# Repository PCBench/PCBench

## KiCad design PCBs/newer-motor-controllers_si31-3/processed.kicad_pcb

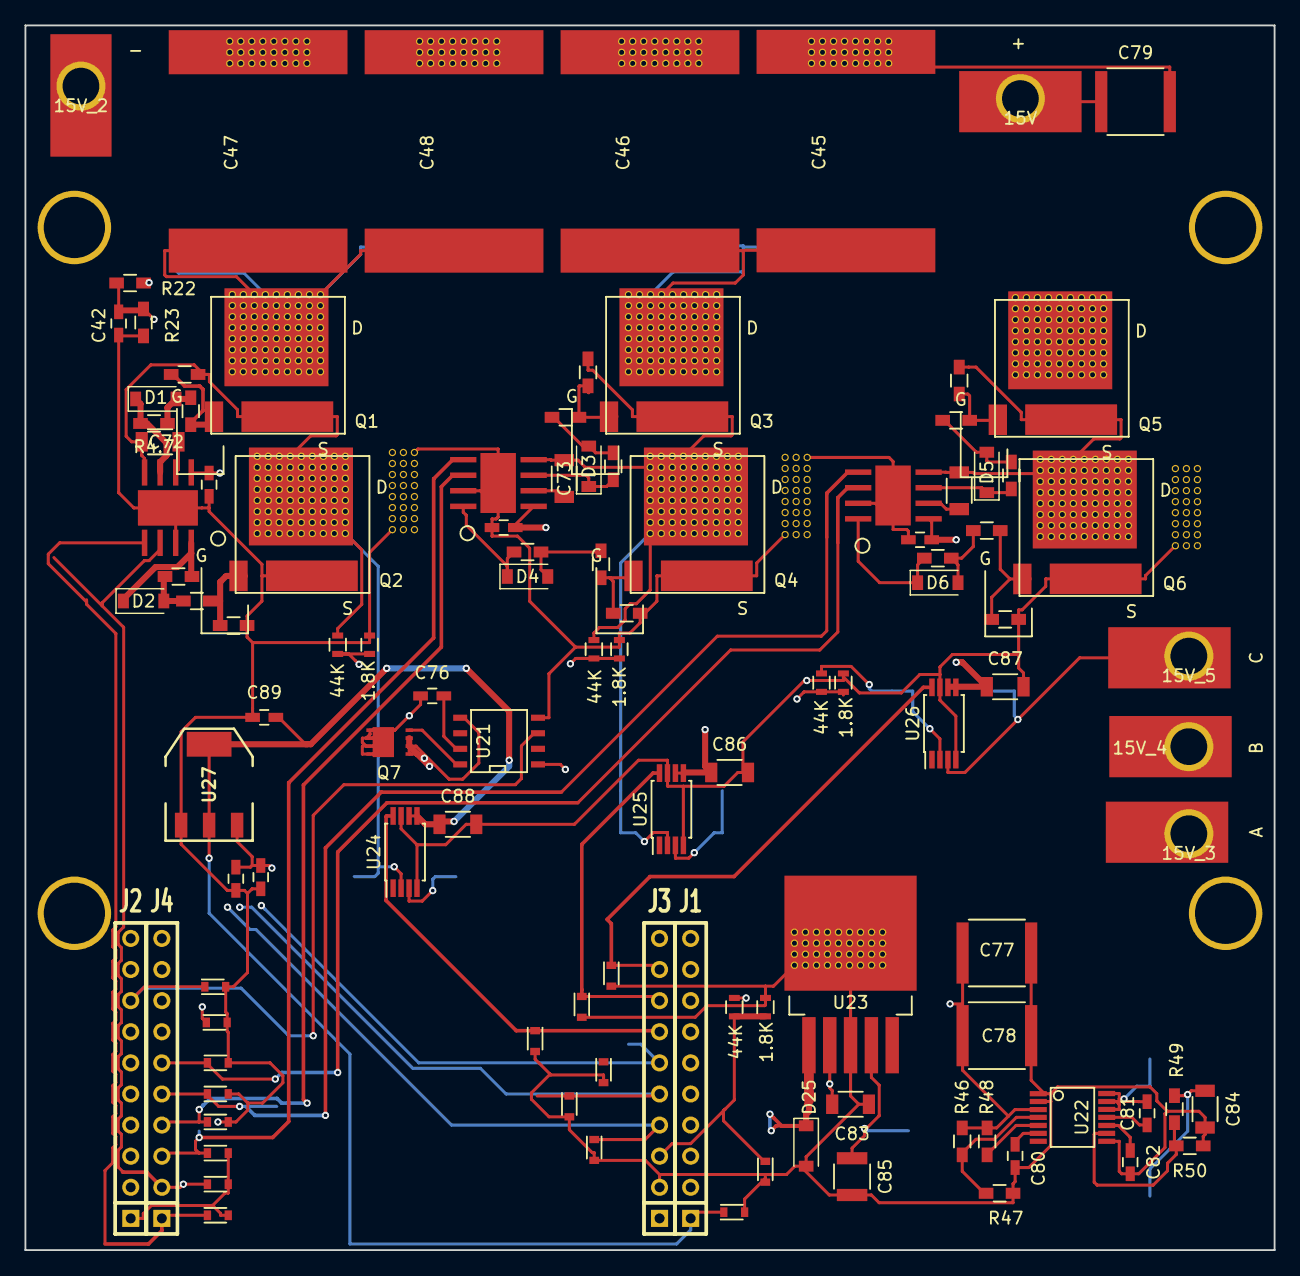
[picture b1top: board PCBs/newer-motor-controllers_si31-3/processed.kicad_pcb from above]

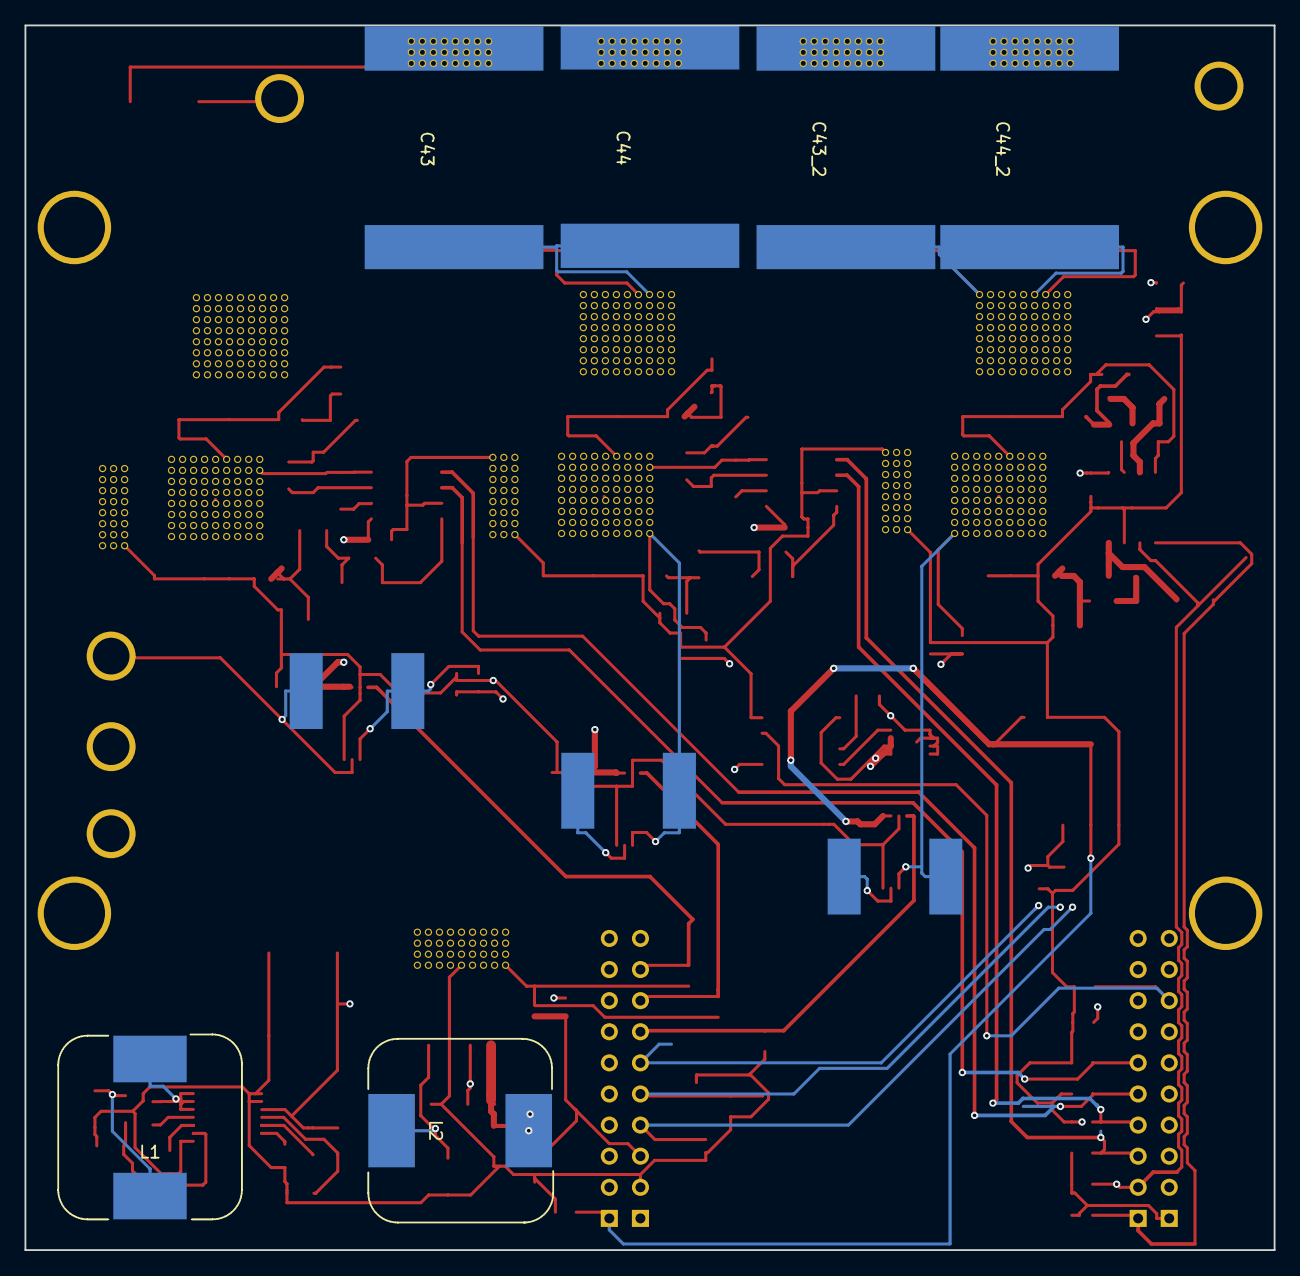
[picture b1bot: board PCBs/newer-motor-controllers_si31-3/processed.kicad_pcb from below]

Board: 4 copper layers, 102.0 x 100.0 mm, 123 parts (9 on the bottom side), 58 nets.

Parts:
10k1, 10k2, 10k3, 10k4, 10k5, 10k6: R_Small; R_0603_HandSoldering
15V, 15V_2, 15V_3, 15V_4, 15V_5: via
+: V+; SolderWirePad_single_SMD_5x10mm
-: V-; SolderWirePad_single_SMD_5x10mm
A: motor_A; SolderWirePad_single_SMD_5x10mm
B: motor_B; SolderWirePad_single_SMD_5x10mm
C: motor_C; SolderWirePad_single_SMD_5x10mm
C42: 2.2uf; C_0603_HandSoldering
C43, C43_2, C44, C44_2, C45, C46, C47, C48: 4.7uf; cap_6065
C69, C70, C71, C82, C89: 1uf; C_0603_HandSoldering
C72, C73, C74, C86, C87, C88: 0.1uf; C_1206
C75: 0.1uf; C_0603_HandSoldering
C76: 10pf; C_0603_HandSoldering
C77, C78, C79: 1uf 250V; C_2220
C80: 22nf; C_0603_HandSoldering
C81: 10nf; C_0603_HandSoldering
C83, C84: 10uf; C_1206
C85: 100uf; C_1210
C90: 10uf; C_0603_HandSoldering
D1, D2, D3, D4, D5, D6: D_Schottky_Small; SOD-123
D8, D9, D10, D11, D12, D13, D14, D15, D16, D17, D18, D19, D20, D21, D22, D23: TVS; D_0603
D25: D_Schottky; SOD-123
J1: Ti_Booster_40_J1; SIL-10J1
J2: Ti_Booster_40_J2; SIL-10J2
J3: Ti_Booster_40_J3; SIL-10J3
J4: Ti_Booster_40_J4; SIL-10J4
L1, L2: INDUCTOR; MSS1583-154KED
Q1, Q2, Q3, Q4, Q5, Q6: FDMT-800; P-PG-HSOF-08
Q7: Q_NMOS_DSG; VSONP-8
R4.1, R4.2, R4.3, R4.4, R4.5, R4.7: R_Small; R_0603_HandSoldering
R22: NTC 10k; R_0603_HandSoldering
R23: 10k; R_0603_HandSoldering
R40, R41, R42, R42_2: 1.8K; R_0603
R43, R44, R45, R45_2: 44K; R_0603
R46: 75k; R_0603_HandSoldering
R47: 4.42k; R_0603_HandSoldering
R48: 499k; R_0603_HandSoldering
R49: 13k; R_0603_HandSoldering
R50: 2k; R_0603_HandSoldering
R51, R52, R53: 0.001R; SHUNT_CSS2H-3920
U18, U19, U20: UCC27210; SO_PowerPAD-8
U21: Si8751; SOIC-8-N
U22: LM5161; SSOP-14
U23: LM2595; TO-263-5Lead
U24, U25, U26: INA240; TSSOP-8_4.4x3mm_Pitch0.65mm
U27: NCP1117ST33T3G; SOT-223
ferrite1, ferrite2, ferrite3, ferrite4, ferrite5, ferrite6: R_Small; R_0603_HandSoldering

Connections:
+5V: C75.1, C85.1, C90.1, J3.1, L2.2, U21.1, U23.4, U27.3
+15V: C76.1, C83.1, C84.1, L1.2, Q7.1, R49.1, U23.2
/Ti_120vgate/vsense_a: D12.1, J3.4, R40.2, R43.2
/Ti_120vgate/vsense_b: D13.1, J3.5, R41.2, R44.2
/Ti_120vgate/vsense_c: J3.6, R42.2, R45.2
/VBUS: 15V.1, +.1, C43.2, C43_2.2, C44.2, C44_2.2, C45.2, C46.2, C47.2, C48.2, C77.1, C78.1, C79.1, Q1.1, Q3.1, Q5.1, R45_2.1, R46.1, R48.2, U22.3
/connector/CurrentA: D15.1, J3.7, U24.8
/connector/CurrentB: D16.1, J3.8, U25.8
/connector/CurrentC: D17.1, J3.9, U26.8
/connector/EN_GATE: D10.1, J2.8, U21.3
/connector/PWM_H1: D18.1, J4.1, U18.5
/connector/PWM_H2: D20.1, J4.3, U19.5
/connector/PWM_H3: D22.1, J4.5, U20.5
/connector/PWM_L1: D19.1, J4.2, U18.6
/connector/PWM_L2: D21.1, J4.4, U19.6
/connector/PWM_L3: D23.1, J4.6, U20.6
/connector/TEMP: C42.1, D8.1, J2.3, R22.2, R23.1
/connector/VBUS_sense: D11.1, J3.3, R42_2.2, R45_2.2
/current_sense_80v/PHASE_1: 15V_3.1, A.1, R53.1, U24.3
/current_sense_80v/PHASE_2: 15V_4.1, B.1, R52.1, U25.3
/current_sense_80v/PHASE_3: 15V_5.1, C.1, R51.1, U26.3
/mosfet/H1: D1.1, R4.7.2, U18.3
/mosfet/H2: D3.1, R4.2.2, U19.3
/mosfet/H3: D5.1, R4.4.2, U20.3
/mosfet/L1: D2.1, R4.1.2, U18.8
/mosfet/L2: D4.1, R4.3.2, U19.8
/mosfet/L3: D6.1, R4.5.2, U20.8
/mosfet/phase_a_in: 10k1.2, C72.1, Q1.2, Q2.1, R43.1, R53.2, U18.4, U24.2
/mosfet/phase_b_in: 10k3.2, C73.1, Q3.2, Q4.1, R44.1, R52.2, U19.4, U25.2
/mosfet/phase_c_in: 10k5.2, C74.1, Q5.2, Q6.1, R45.1, R51.2, U20.4, U26.2
GND: 10k2.2, 10k4.2, 10k6.2, 15V_2.1, -.1, C42.2, C43.1, C43_2.1, C44.1, C44_2.1, C45.1, C46.1, C47.1, C48.1, C69.2, C70.2, C71.2, C75.2, C77.2, C78.2, C79.2, C80.2, C82.2, C83.2, C84.2, C85.2, C86.2, C87.2, C88.2, C89.2, C90.2, D8.2, D9.2, D10.2, D11.2, D12.2, D13.2, D14.2, D15.2, D16.2, D17.2, D18.2, D19.2, D20.2, D21.2, D22.2, D23.2, D25.2, J2.1, J3.2, Q2.2, Q4.2, Q6.2, R23.2, R40.1, R41.1, R42.1, R42_2.1, R47.2, R50.2, U18.7, U18.pad, U19.7, U19.pad, U20.7, U20.pad, U21.4, U22.1, U22.2, U22.8, U23.3, U24.4, U24.7, U25.4, U25.7, U26.4, U26.7, U27.1
unnamed: 10k1.1, Q1.3, ferrite1.1
unnamed: 10k2.1, Q2.3, ferrite2.1
unnamed: 10k3.1, Q3.3, ferrite3.1
unnamed: 10k4.1, Q4.3, ferrite4.1
unnamed: 10k5.1, Q5.3, ferrite5.1
unnamed: 10k6.1, Q6.3, ferrite6.1
unnamed: C69.1, C70.1, C71.1, Q7.2, U18.1, U19.1, U20.1, U21.5
unnamed: C72.2, U18.2
unnamed: C73.2, U19.2
unnamed: C74.2, U20.2
unnamed: C76.2, U21.7
unnamed: C80.1, U22.6
unnamed: C81.1, L1.1, U22.12, U22.13, U22.14
unnamed: C81.2, U22.11
unnamed: C82.1, U22.10
unnamed: C86.1, C87.1, C88.1, C89.1, D9.1, J1.1, R22.1, U24.5, U24.6, U25.5, U25.6, U26.5, U26.6, U27.2
unnamed: D1.2, R4.7.1, ferrite1.2
unnamed: D2.2, R4.1.1, ferrite2.2
unnamed: D3.2, R4.2.1, ferrite3.2
unnamed: D4.2, R4.3.1, ferrite4.2
unnamed: D5.2, R4.4.1, ferrite5.2
unnamed: D6.2, R4.5.1, ferrite6.2
unnamed: D25.1, L2.1, U23.1
unnamed: Q7.3, U21.8
unnamed: R46.2, R47.1, U22.4
unnamed: R48.1, U22.5
unnamed: R49.2, R50.1, U22.9

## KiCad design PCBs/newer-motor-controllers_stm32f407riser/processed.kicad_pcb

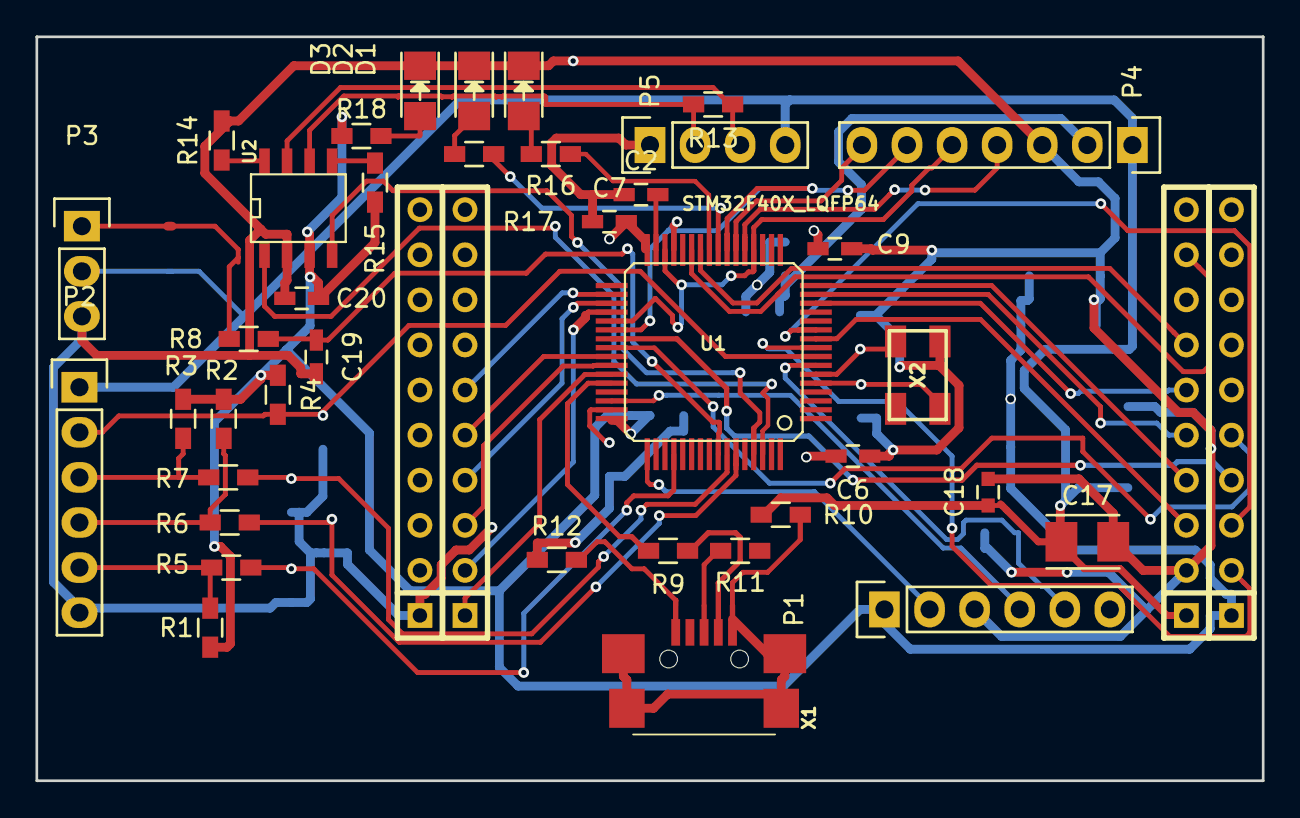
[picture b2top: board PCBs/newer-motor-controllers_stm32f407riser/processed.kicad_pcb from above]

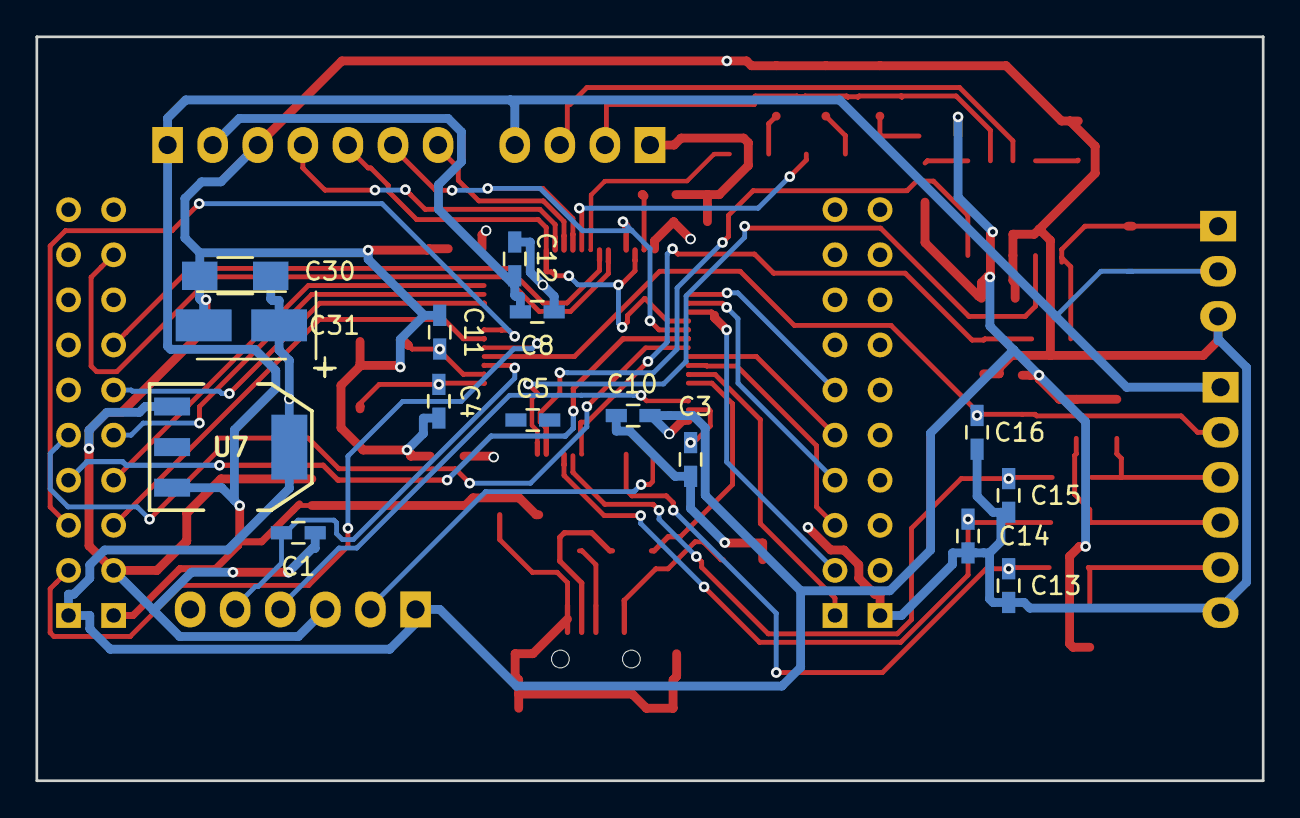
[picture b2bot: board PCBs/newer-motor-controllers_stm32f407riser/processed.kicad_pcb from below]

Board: 4 copper layers, 69.1 x 41.9 mm, 57 parts (15 on the bottom side), 55 nets.

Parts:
C1: 100pf; C_0603_HandSoldering
C2, C3, C5, C6, C7, C8, C9, C10, C12, C20: 2.2uf; C_0603_HandSoldering
C4, C11: 15pf; C_0603_HandSoldering
C13, C14, C15, C16: 4.7nf; C_0603_HandSoldering
C17: 100uf; TantalC_SizeB_EIA-3528_Reflow
C18: 10uf; C_0603
C19: 100nf; C_0603_HandSoldering
C30: 2.2uf; C_1206_HandSoldering
C31: 100uf; TantalC_SizeB_EIA-3528_HandSoldering
D1, D2, D3: LED; LED_1206
J1: Ti_Booster_40_J1; SIL-10J1
J2: Ti_Booster_40_J2; SIL-10J2
J3: Ti_Booster_40_J3; SIL-10J3
J4: Ti_Booster_40_J4; SIL-10J4
P1, P2: CONN_01X06; Pin_Header_Straight_1x06
P3: CONN_01X03; Pin_Header_Straight_1x03
P4: CONN_01X07; Pin_Header_Straight_1x07
P5: CONN_01X04; Pin_Header_Straight_1x04
R1, R2, R3, R8, R18: 2k; R_0603_HandSoldering
R4, R5, R6, R7, R14, R15: 10k; R_0603_HandSoldering
R9, R11: 20r; R_0603_HandSoldering
R10, R12: 0r; R_0603_HandSoldering
R13: 120R; R_0603_HandSoldering
R16, R17: 100r; R_0603_HandSoldering
U1: STM32F40X_LQFP64; lqfp64_pad_mod_hand
U2: MCP2551-I/SN; SOIC-8-W
U7: NCP1117ST33T3G; SOT-223
X1: MINI-USB-SCHIELD-32005-201; USB-UX60R-MB-5ST
X2: 8MHz 10ppm; Crystal_5x3mm

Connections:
+3V3: C6.2, C7.2, C8.2, C9.2, C10.1, C12.1, C20.1, C30.1, C31.1, J1.1, P1.1, P4.2, R1.1, R2.1, R3.1, R4.1, R15.1, R18.2, U1.32, U1.48, U2.3, U7.2
+5V: C17.1, C18.1, J3.1, P2.1, P3.2, P4.1, P5.4, R10.1, U7.3
/Power MOSFETS/CAN_RX: U1.61, U2.4
/Power MOSFETS/CAN_TX: U1.62, U2.1
/Power MOSFETS/CurrentA: J3.7, U1.26
/Power MOSFETS/CurrentC: J3.9, U1.27
/Power MOSFETS/H1: J4.1, U1.43
/Power MOSFETS/H2: J4.3, U1.42
/Power MOSFETS/H3: J4.5, U1.41
/Power MOSFETS/HALL_1: C15.1, R7.1, U1.58
/Power MOSFETS/HALL_2: C14.1, R6.1, U1.59
/Power MOSFETS/HALL_3: C13.1, R5.1, U1.52
/Power MOSFETS/L1: J4.2, U1.36
/Power MOSFETS/L2: J4.4, U1.35
/Power MOSFETS/L3: J4.6, U1.34
/Power MOSFETS/LED_GREEN: R16.2, U1.25
/Power MOSFETS/LED_RED: R17.2, U1.24
/Power MOSFETS/MISO_ADC_EXT: P4.7, U1.22
/Power MOSFETS/PC1: J1.2, U1.9
/Power MOSFETS/PC3: J1.3, U1.11
/Power MOSFETS/PC8: J1.4, U1.39
/Power MOSFETS/PC9: J1.5, U1.40
/Power MOSFETS/RX_SCL_MOSI: P4.6, U1.23, U1.29, U1.38
/Power MOSFETS/SCK_ADC_EX: P4.4, U1.21
/Power MOSFETS/SERVO: C19.2, R8.2, U1.57
/Power MOSFETS/TEMP_MOTOR: C16.1, P2.2, R4.2, U1.8
/Power MOSFETS/TX_SDA_NSS: P4.5, U1.20, U1.30, U1.37
/Power MOSFETS/USB_DM: R9.2, U1.44
/Power MOSFETS/VBUS_SENSE: J3.3, U1.10
/Power MOSFETS/V_SENSE1: J3.4, U1.16
/Power MOSFETS/V_SENSE2: J3.5, U1.15
/Power MOSFETS/V_SENSE3: J3.6, U1.14
GND: C1.1, C2.1, C3.1, C4.1, C6.1, C7.1, C8.1, C9.1, C10.2, C11.1, C12.2, C13.2, C14.2, C15.2, C16.2, C17.2, C18.2, C19.1, C20.2, C30.2, C31.2, D1.1, D2.1, D3.1, J2.1, J3.2, P1.3, P2.6, P3.3, P4.3, P5.1, R12.1, R14.2, U2.2, U7.1, X2.3
unnamed: C1.2, P1.5, U1.7
unnamed: C2.2, U1.31
unnamed: C3.2, U1.47
unnamed: C4.2, U1.5, X2.1
unnamed: C11.2, U1.6, X2.2
unnamed: D1.2, R16.1
unnamed: D2.2, R17.1
unnamed: D3.2, R18.1
unnamed: P1.2, U1.49
unnamed: P1.4, U1.46
unnamed: P2.3, R3.2, R7.2
unnamed: P2.4, R2.2, R6.2
unnamed: P2.5, R1.2, R5.2
unnamed: P3.1, R8.1
unnamed: P5.2, R13.2, U2.6
unnamed: P5.3, R13.1, U2.7
unnamed: R9.1, X1.2
unnamed: R10.2, X1.1, X1.5
unnamed: R11.1, X1.3
unnamed: R12.2, X1.5
unnamed: R14.1, U2.8
unnamed: R15.2, U2.5

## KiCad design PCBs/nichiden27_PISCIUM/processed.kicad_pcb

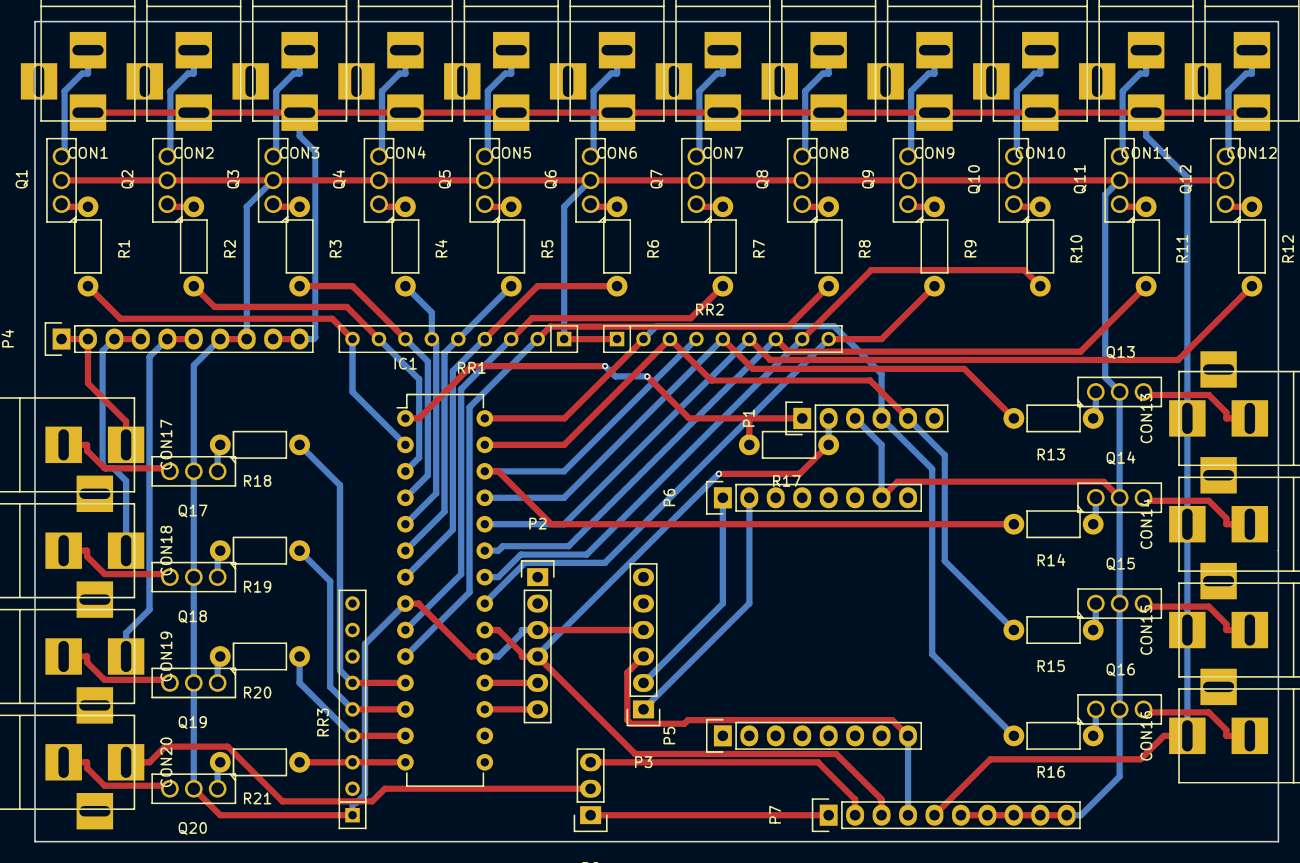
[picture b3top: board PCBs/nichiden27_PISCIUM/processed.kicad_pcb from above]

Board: 2 copper layers, 119.4 x 78.7 mm, 73 parts (0 on the bottom side), 75 nets.

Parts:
CON1, CON2, CON3, CON4, CON5, CON6, CON7, CON8, CON9, CON10, CON11, CON12, CON13, CON14, CON15, CON16, CON17, CON18, CON19, CON20: BARREL_JACK
IC1: PIC16F1938; DIP-28_W7.62mm
P1, P2, P3: CONN_01X06; Pin_Header_Straight_1x06
P4, P7: CONN_01X10; Pin_Header_Straight_1x10
P5, P6: CONN_01X08; Pin_Header_Straight_1x08
P8: GINGA_voltage_selector; Pin_Header_Straight_1x03
Q1, Q2, Q3, Q4, Q5, Q6, Q7, Q8, Q9, Q10, Q11, Q12, Q13, Q14, Q15, Q16, Q17, Q18, Q19, Q20: EKI04047; SOT126_SOT32_Housing_Vertical
R1, R2, R3, R4, R5, R6, R7, R8, R9, R10, R11, R12, R13, R14, R15, R16, R18, R19, R20, R21: 100; Resistor_Horizontal_RM7mm
R17: 4.7k-10k; Resistor_Horizontal_RM7mm
RR1, RR2, RR3: RR8_100k; Resistor_Array_SIP8

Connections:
3.3V_LOGIC: P3.3, P5.8, P7.4
5V_GINGA: P7.1, P8.1
5V_ITTOU1: CON19.1, P4.5, P4.6
5V_LOGIC: IC1.20, P1.2, P2.4, P7.3, R17.1
12V_GINGA: P7.2, P8.3
12V_KOUTOU11: CON17.1, P4.1, P4.2
12V_KOUTOU21: CON18.1, P4.3, P4.4
12V_SEIZAE1: CON1.1, CON2.1, CON3.1, CON4.1, CON5.1, CON6.1, CON7.1, CON8.1, CON9.1, CON10.1, CON11.1, CON12.1, CON13.1, CON14.1, CON15.1, CON16.1, P4.9, P4.10, P7.5
+12V: IC1.8, IC1.19, P1.3, P2.3, P3.4, P4.7, P4.8, P6.7, P7.6, P7.7, P7.8, P7.9, P7.10, Q1.2, Q2.2, Q3.2, Q4.2, Q5.2, Q6.2, Q7.2, Q8.2, Q9.2, Q10.2, Q11.2, Q12.2, Q13.2, Q14.2, Q15.2, Q16.2, Q17.2, Q18.2, Q19.2, Q20.2, RR1.1, RR2.1, RR3.1
unnamed: CON1.2, Q1.3
unnamed: CON2.2, Q2.3
unnamed: CON3.2, Q3.3
unnamed: CON4.2, Q4.3
unnamed: CON5.2, Q5.3
unnamed: CON6.2, Q6.3
unnamed: CON7.2, Q7.3
unnamed: CON8.2, Q8.3
unnamed: CON9.2, Q9.3
unnamed: CON10.2, Q10.3
unnamed: CON11.2, Q11.3
unnamed: CON12.2, Q12.3
unnamed: CON13.2, Q13.3
unnamed: CON14.2, Q14.3
unnamed: CON15.2, Q15.3
unnamed: CON16.2, Q16.3
unnamed: CON17.2, Q17.3
unnamed: CON18.2, Q18.3
unnamed: CON19.2, Q19.3
unnamed: CON20.2, Q20.3
unnamed: IC1.1, P1.1, R17.2
unnamed: IC1.2, R1.2, RR1.9
unnamed: IC1.3, R2.2, RR1.8
unnamed: IC1.4, R3.2, RR1.7
unnamed: IC1.5, R4.2, RR1.6
unnamed: IC1.6, R5.2, RR1.5
unnamed: IC1.7, R6.2, RR1.4
unnamed: IC1.9, R7.2, RR1.3
unnamed: IC1.10, R8.2, RR1.2
unnamed: IC1.11, R18.1, RR3.6
unnamed: IC1.12, R19.1, RR3.5
unnamed: IC1.13, R20.1, RR3.4
unnamed: IC1.14, R21.1, RR3.3
unnamed: IC1.17, P2.6
unnamed: IC1.18, P2.5
unnamed: IC1.21, R9.2, RR2.9
unnamed: IC1.22, R10.2, RR2.8
unnamed: IC1.23, R11.2, RR2.7
unnamed: IC1.24, R12.2, RR2.6
unnamed: IC1.25, R13.2, RR2.5
unnamed: IC1.26, R14.2, RR2.4
unnamed: IC1.27, P1.5, R15.2, RR2.3
unnamed: IC1.28, P1.4, R16.2, RR2.2
unnamed: P3.1, P6.2
unnamed: P3.2, P6.1
unnamed: Q1.1, R1.1
unnamed: Q2.1, R2.1
unnamed: Q3.1, R3.1
unnamed: Q4.1, R4.1
unnamed: Q5.1, R5.1
unnamed: Q6.1, R6.1
unnamed: Q7.1, R7.1
unnamed: Q8.1, R8.1
unnamed: Q9.1, R9.1
unnamed: Q10.1, R10.1
unnamed: Q11.1, R11.1
unnamed: Q12.1, R12.1
unnamed: Q13.1, R13.1
unnamed: Q14.1, R14.1
unnamed: Q15.1, R15.1
unnamed: Q16.1, R16.1
unnamed: Q17.1, R18.2
unnamed: Q18.1, R19.2
unnamed: Q19.1, R20.2
unnamed: Q20.1, R21.2
VCC_GINGA: CON20.1, P8.2

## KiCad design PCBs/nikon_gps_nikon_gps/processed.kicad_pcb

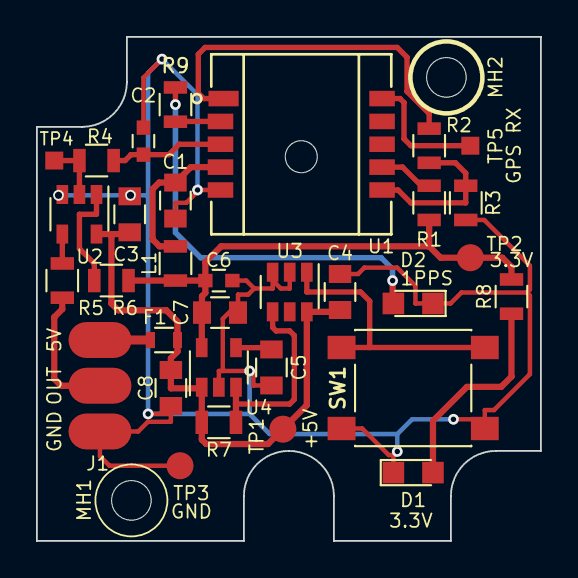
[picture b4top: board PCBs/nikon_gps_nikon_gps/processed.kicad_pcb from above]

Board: 2 copper layers, 28.0 x 28.0 mm, 34 parts (0 on the bottom side), 20 nets.

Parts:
C1, C3, C4: 100nF; C_0805
C2: 18pF; C_0603
C5: 470pF; C_0805
C6: 1nF; C_0603
C7, C8: 10uF; C_0805
D1: Red; LED_0805
D2: Blue; LED_0805
F1: 0.1A; R_0603
J1: Conn_01x03; Connection_Pads_03
L1: 600Ohm; L_0805
MH1, MH2: M2 screw; MountingHole_2.2mm_M2_DIN965
R1, R3: 10K; R_0805
R2, R4, R5: 33; R_0805
R6, R7: 0; R_0805
R8: 330; R_0805
R9: 270; R_0805
SW1: ON/OFF; SW_SPST_PTS645
TP1: 5V; Measurement_Point_Round-SMD-Pad_Small
TP2: 3.3V; Measurement_Point_Round-SMD-Pad_Small
TP3: GND; Measurement_Point_Round-SMD-Pad_Small
TP4: GPS TX; Measurement_Point_Square-SMD_1.0mmx1.0mm
TP5: GPS RX; Measurement_Point_Square-SMD_1.0mmx1.0mm
U1: Hornet ORG1411; ORG1411_GPS
U2: SN74LV1T126_ALT; SOT-23-5
U3: MAX16054; SOT-23-6
U4: MIC5205-3.3; SOT-23-5

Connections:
+3V3: C6.1, C7.1, L1.2, R1.1, R6.1, R8.2, TP2.1, U4.5
+5V: C3.2, C4.2, C8.1, F1.1, R7.2, TP1.1, U2.5, U3.6, U4.1
/1PPS: R9.2, U1.2
/3.3V_EN: R7.1, U3.4, U4.3
/3.3V_GPS: C1.2, L1.1, U1.4
/BUF_EN: R6.2, U2.1
/BUF_IN: R4.2, TP4.1, U2.2
/BUF_OUT: R5.1, U2.4
/C_BYP: C5.1, U4.4
/GPS_OUT: J1.2, R5.2
/GPS_RX: TP5.1, U1.10
/GPS_TX: C2.1, R4.1, U1.3
/ON_OFF: R2.2, U1.1
/ON_SW: SW1.2, U3.1
/WAKEUP: R2.1, R3.1, U1.6
/~CTS: R1.2, U1.7
GND: C1.1, C2.2, C3.1, C4.1, C5.2, C6.2, C7.2, C8.2, D1.1, D2.1, J1.3, R3.2, SW1.1, TP3.1, U1.5, U2.3, U3.2, U3.3, U4.2
unnamed: D1.2, R8.1
unnamed: D2.2, R9.1
unnamed: F1.2, J1.1

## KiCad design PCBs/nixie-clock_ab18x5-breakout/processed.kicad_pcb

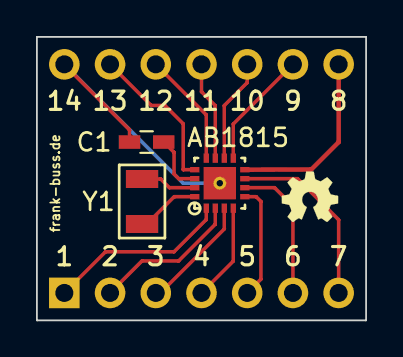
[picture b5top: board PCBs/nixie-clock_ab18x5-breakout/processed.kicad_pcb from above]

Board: 2 copper layers, 18.3 x 15.7 mm, 5 parts (0 on the bottom side), 17 nets.

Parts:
C1: 47pF; C_0603_HandSoldering
J1: CONN_01X07; Pin_Header_Straight_1x07_Pitch2.54mm2
J2: CONN_01X07; Pin_Header_Straight_1x07_Pitch2.54mm
U1: AB1815; qfn16
Y1: Crystal; crystal

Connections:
/CLKOUT/nIRQ3: J2.7, U1.8
/EXTI: J2.5, U1.10
/FOUT/nIRQ: J2.4, U1.11
/PSW/nIRQ2: J1.4, U1.4
/SCL: J1.7, U1.7
/SDI: J2.6, U1.9
/SDO: J1.6, U1.6
/VBAT: J1.5, U1.5
/VCC: J2.2, U1.13
/WDI: J1.2, U1.2
/nCE: J2.3, U1.12
/nEXTR: J1.3, U1.3
/nRST: J1.1, U1.1
GND: C1.2, J2.1, U1.PAD
unnamed: C1.1, U1.14
unnamed: U1.15, Y1.2
unnamed: U1.16, Y1.1
